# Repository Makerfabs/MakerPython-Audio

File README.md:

# MakerPython-Audio

```c++
/*
Version:		V2.0
Author:			UNKOWN
Create Date:	UNKOWN
Note:
	2020/7/24	v2.0: Rebuid readme,add pic. By Vincent
*/
```

[toc]

# Introduce

The MakePython Audio board uses the uDA1334 digital to analog converter (DAC), which converts I2S (not be confused with I2C) audio to an analog signal to drive speakers. The I2S Audioboard converts the digital audio signals using the I2S standard to an analog signal.

- You can get one from: [MakePython_Audio](https://www.makerfabs.com/makepython-audio.html)

- Hardware and detailed instructions please visit Wiki page:  [MakePython_Audio Wiki](https://www.makerfabs.com/wiki/index.php?title=MakePython_Audio)

# Related Projects

## [Project_MakePython_Audio_Music](https://github.com/Makerfabs/Project_MakePython_Audio_Music)

- Make a music player by yourself.
- [YOUTUBE:MakePython Audio Music Play](https://www.youtube.com/watch?v=0urJ_uxfW0k&feature=youtu.be)

## [Project_TTS-Weather-Broadcast](https://github.com/Makerfabs/Project_TTS-Weather-Broadcast)

- Internet weather voice broadcast by TTS(Text to Speech).
- [YOUTUBE:TTS-Weather-Broadcast](https://youtu.be/00nAEQKYFV4)

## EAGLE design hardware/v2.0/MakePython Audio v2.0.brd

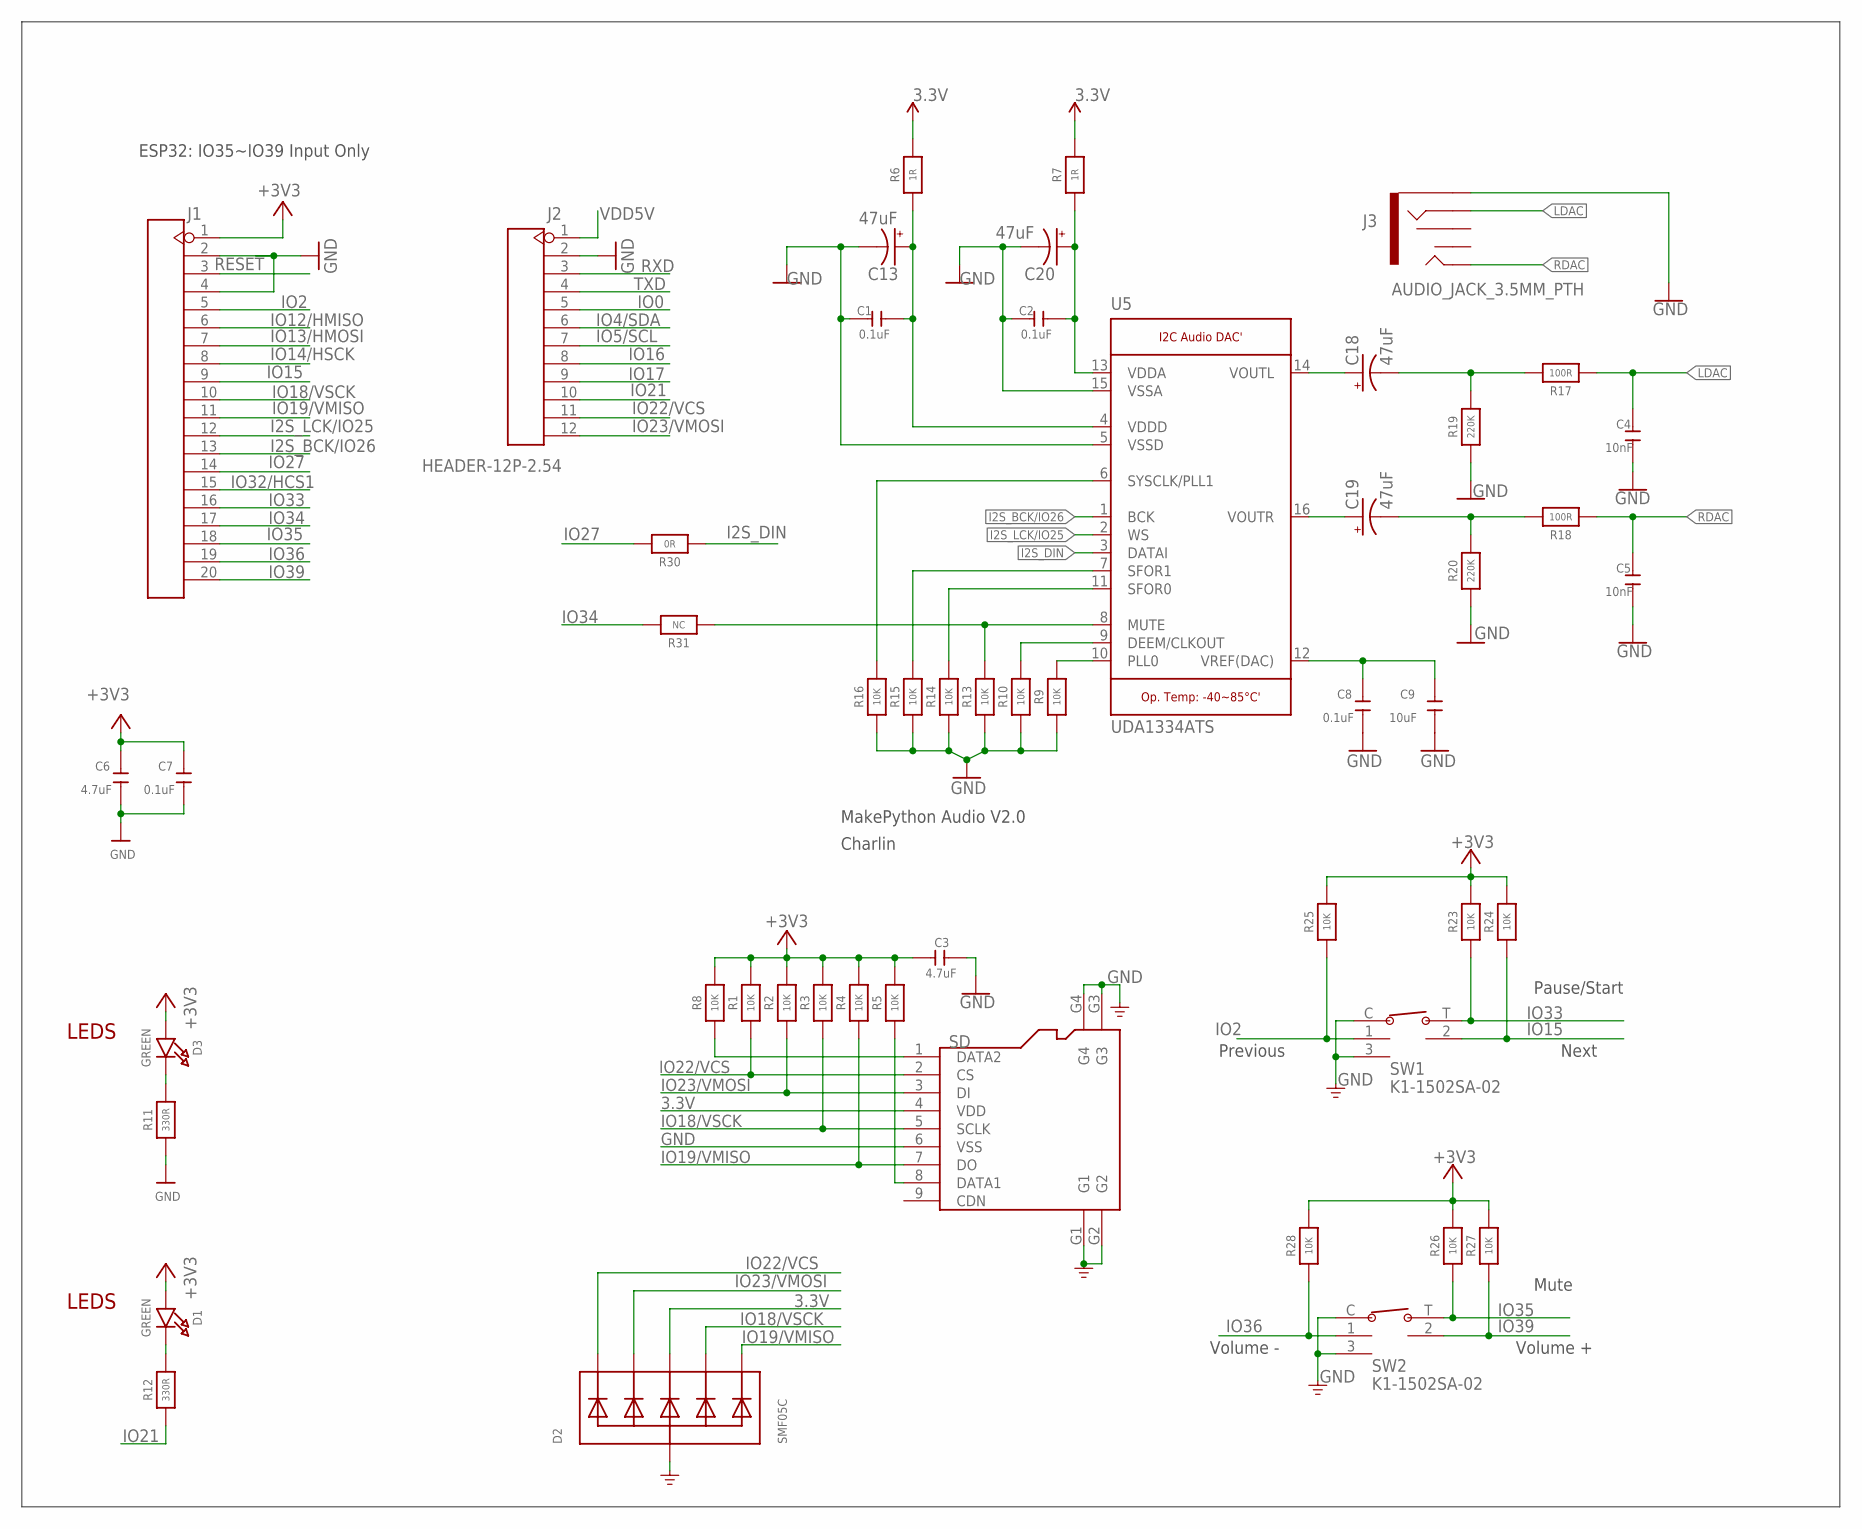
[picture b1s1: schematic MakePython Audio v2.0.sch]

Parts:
C1, C2, C7, C8: 0.1uF; DISCRETE_C0603
C3, C6: 4.7uF; DISCRETE_C0603
C4, C5: 10nF; DISCRETE_C0603
C9: 10uF; DISCRETE_C0603
C13, C18, C19, C20: 47uF; EIA3528
D1, D3: GREEN; CHIPLED_0805_NOOUTLINE
D2: SMF05C; SOT363
J1: HEADER-20P-2.54; 20P-2.54
J2: HEADER-12P-2.54; 12P-2.54
J3: AUDIO_JACK_3.5MM_PTH; AUDIO-JACK
R1, R2, R3, R4, R5, R8, R9, R10, R13, R14, R15, R16, R23, R24, R25, R26, R27, R28: 10K; 0603-NO
R6, R7: 1R; 0603-NO
R11, R12: 330R; 0603-NO
R17, R18: 100R; 0603-NO
R19, R20: 220K; 0603-NO
R30: 0R; 0603-NO
R31: NC; 0603-NO
SD: HOLDER-MICROSD-9P; 9P-SMD-W/-RING
SW1, SW2: K1-1502SA-02; SMD5-60P-1180L1170W
U5: UDA1334ATS; MICROBUILDER_SSOP16_4.4MM

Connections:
3.3V: C3.2, C6.2, C7.2, D1.A, D2.4 (C3), D3.A, J1.1, R1.2, R2.2, R3.2, R4.2, R5.2, R6.2, R7.2, R8.2, R23.2, R24.2, R25.2, R26.2, R27.2, R28.2, SD.4 (VDD)
GND: C1.2, C2.2, C3.1, C4.1, C5.1, C6.1, C7.1, C8.1, C9.1, C13.C (-), C20.C (-), D2.2 (A), J1.2, J1.4, J2.2, J3.SLEEVE, R9.1, R10.1, R11.1, R13.1, R14.1, R15.1, R16.1, R19.1, R20.1, SD.6 (VSS), SD.G1, SD.G2, SD.G3, SD.G4, SW1.3, SW1.C, SW2.3, SW2.C, U5.5 (VSSD), U5.15 (VSSA)
I2S_BCK/IO26: J1.13, U5.1 (BCK)
I2S_DIN: R30.1, U5.3 (DATAI)
I2S_LCK/IO25: J1.12, U5.2 (WS)
IO0: J2.5
IO2: J1.5, R25.1, SW1.1
IO4/SDA: J2.6
IO5/SCL: J2.7
IO12/HMISO: J1.6
IO13/HMOSI: J1.7
IO14/HSCK: J1.8
IO15: J1.9, R24.1, SW1.2
IO16: J2.8
IO17: J2.9
IO18/VSCK: D2.5 (C4), J1.10, R3.1, SD.5 (SCLK)
IO19/VMISO: D2.6 (C5), J1.11, R4.1, SD.7 (DO)
IO21: J2.10, R12.1
IO22/VCS: D2.1 (C1), J2.11, R1.1, SD.2 (CS)
IO23/VMOSI: D2.3 (C2), J2.12, R2.1, SD.3 (DI)
IO27: J1.14, R30.2
IO32/HCS1: J1.15
IO33: J1.16, R23.1, SW1.T
IO34: J1.17, R31.2
IO35: J1.18, R26.1, SW2.T
IO36: J1.19, R28.1, SW2.1
IO39: J1.20, R27.1, SW2.2
LDAC: C4.2, J3.RING, R17.1
unnamed: R8.1, SD.1 (DATA2)
unnamed: R5.1, SD.8 (DATA1)
unnamed: D1.C, R12.2
unnamed: D3.C, R11.2
unnamed: C18.A (+), U5.14 (VOUTL)
unnamed: C19.A (+), U5.16 (VOUTR)
unnamed: C18.C (-), R17.2, R19.2
unnamed: C19.C (-), R18.2, R20.2
unnamed: C2.1, C20.A (+), R7.1, U5.13 (VDDA)
unnamed: C1.1, C13.A (+), R6.1, U5.4 (VDDD)
unnamed: R16.2, U5.6 (SYSCLK/PLL1)
unnamed: R15.2, U5.7 (SFOR1)
unnamed: R14.2, U5.11 (SFOR0)
unnamed: R13.2, R31.1, U5.8 (MUTE)
unnamed: R10.2, U5.9 (DEEM/CLKOUT)
unnamed: R9.2, U5.10 (PLL0)
unnamed: C8.2, C9.2, U5.12 (VREF(DAC))
RDAC: C5.2, J3.TIP, R18.1
RESET: J1.3
RXD: J2.3
TXD: J2.4
VDD5V: J2.1

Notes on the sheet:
ESP32: IO35~IO39 Input Only
MakePython Audio V2.0
LEDS
Charlin
Previous
Next
Pause/Start
Volume +
Volume -
Mute

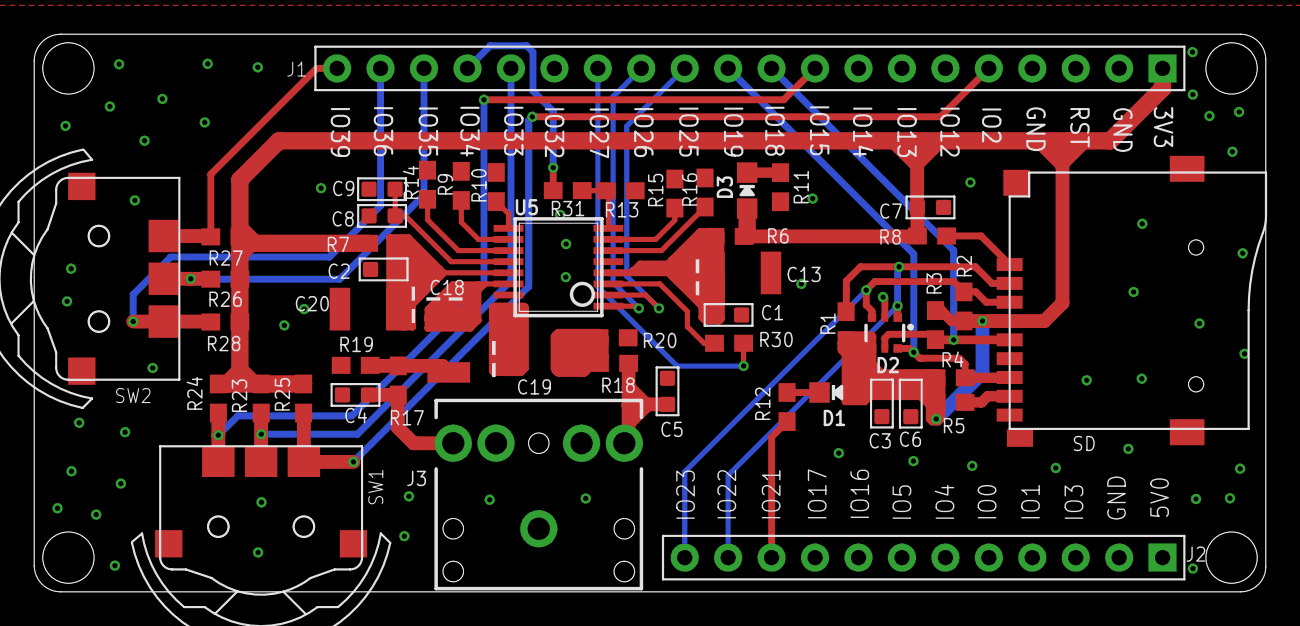
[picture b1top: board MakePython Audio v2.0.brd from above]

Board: 2 copper layers, 71.9 x 32.5 mm, 52 parts (1 on the bottom side), 37 nets.

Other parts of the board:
U$1: MAKERFABS_0.3

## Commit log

2020-07-02 Add files via upload
    text to speech
2020-07-24 rebuild readme
2020-09-15 add hardware

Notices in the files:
parts and their libraries:
microbuilder: This work is placed in the public domain, and may be freely used for commercial and non-commercial work with the following conditions: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
SparkFun-Connectors: Licensing: Creative Commons ShareAlike 4.0 International - https://creativecommons.org/licenses/by-sa/4.0
